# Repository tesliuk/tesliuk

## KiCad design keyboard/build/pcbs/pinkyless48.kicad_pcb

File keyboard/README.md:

# pinkyless48

A 48-key column-staggered split keyboard, designed around barely using your
pinkies. Kailh Choc v1 low-profile, hotswap, wired, RP2040 + QMK.

## The layout

24 keys per half:

```
 pinky  ring   mid   idx  inner
   O      O     O     O     O                  number row
   O      O     O     O     O                  top row
   O      O     O     O     O                  home row
   ·      O     O     O     O                  bottom row

                            O     O     O      thumb arc
                               O     O         thumb island
```

The thumb cluster starts where the finger matrix ends: the nearest thumb key
sits directly below the innermost finger column, and the cluster runs inboard
from there rather than being tucked back underneath the fingers.

The pinky drops only the **bottom row**, the position it reaches worst. It
keeps number, top and home. Because the number row therefore has all five
columns, it carries a full `1234567890` across the two halves and digits need
no layer. Z, Shift, Ctrl, Tab, Esc, Enter and Backspace — the rest of what a
pinky normally carries — moved to the thumbs and to home-row mods.

Five thumb keys per half, in two groups: a 3-key arc that follows the thumb's
natural sweep inboard and down, and a 2-key island tucked below it for the
keys you press less often. The furthest is 42 mm from the thumb home key,
inside the ~45 mm a relaxed thumb can sweep without the hand leaving position.

Column stagger is deliberately flat: inner, index and ring all sit level with
each other, middle is 4 mm further forward, and pinky drops **12 mm** back.
This is not the usual finger-length stagger — only the middle finger gets
extra reach.

The pinky drop is larger than it looks like it needs to be, on purpose. That
column carries three keys and skips the *bottom* row, so its block occupies
the upper three row positions. With a small stagger the column reads as
sitting higher than its neighbours even though every individual key is lower;
12 mm brings the whole block down to where a short finger actually rests.

One consequence worth knowing: the reversible Choc hotswap footprint carries
socket pads for *both* faces of the board and is ±9.58 mm wide, so two columns
at the *same* height short against each other at an 18 mm pitch. Index and
inner are level, so that single gap is opened to **19.8 mm**. Every other gap
stays at 18 mm, clearing on vertical offset alone.

Key pitch is **18.5 × 18 mm**, slightly looser than the 18 × 17 Choc standard.
Stock spacing leaves only 0.5 mm between MBK keycaps and 2.0 mm between switch
flanges, which works but is tight for getting a puller in and leaves nothing
for caps larger than MBK. This gives 1.0 mm between caps, 1.5 mm down rows and
3.0 mm between flanges, for ~2 mm of width and ~3 mm of height.

Board: **141 × 138 mm** per half. Case: **8.9 mm** tall before switches.
The width comes from the thumb cluster reaching ~37 mm inboard of the matrix.

The controller, TRRS jack and reset button live in the **notch** between the
finger matrix and the thumb cluster, not on a strip above the matrix. Because
the thumb cluster runs inboard and down, that area is dead space already
inside the bounding box, so the controller costs nothing in overall size —
putting it above the matrix instead added 30 mm of board height for a part
that is 33 × 18 mm. The USB port faces inboard, so the cable exits between
the halves.

The board silhouette is built from **three simple shapes**, not from one
rectangle per key: the finger matrix as a single rectangle, the thumb cluster
as a hull over its five keys, and the controller area as a rectangle. Unioning
24 key pads plus a rotated thumb cluster used to produce an outline of ~50
entities full of little scallops and fillets, which is miserable to build a
case against. The result now is **9 straight lines and 12 arcs**, for about
1 cm² more copper.

The union is then **morphologically closed** (grown 18 mm, shrunk 18 mm) before
filleting. That fills the concave pockets between the thumb cluster, the
controller area and the key pads — dead space whose sharp inside corners are
crack initiation points in both FR4 and the printed plate. It costs 1.3% more
board area and nothing in bounding box, and keeps the narrowest neck above 50 mm. Each half is closed separately —
closing them together would bridge the gap between the halves and fuse them. A plain convex hull would have swallowed the whole empty
region left of the thumb cluster and added ~40 cm² of pointless board.

## What is in here

```
src/config.yaml        the single source of truth - layout, nets, footprints
src/check_*.py         five verification passes, run by `make check`
src/find_mounts.py     searches the board for valid screw positions
case/gen_case.py       plate + tray STLs, generated from the same key positions
firmware/gen_qmk.py    generates keyboard.json from the same key positions
firmware/pinkyless48/  QMK keymap
build/                 generated outputs (committed - they are the deliverable)
docs/ORDERING.md       how to get it made with almost no soldering
docs/PIN_MAPPING.md    controller pins, matrix cells, debugging a bad matrix
```

Everything downstream — PCB, case, firmware — is derived from `src/config.yaml`.
Change a dimension there, run `make`, and the board, the STLs and the keymap
all follow. Nothing is hand-maintained in two places.

## Build it

```sh
make deps      # npm install + python deps
make           # build, check, case, firmware
```

`make check` runs five passes and fails loudly:

| Check | Catches |
|-------|---------|
| `layout` | **minimum** keycap and switch-flange gaps (not just overlap), for two cap sizes; thumb keys out of reach |
| `outline` | disconnected pieces; stray voids; missing screw holes; **thin necks and concave notches** |
| `matrix` | miswired switch/diode; **two keys sharing a matrix cell** |
| `fit` | components or screws hanging off the board edge |
| `shorts` | **pads on different nets overlapping**; copper clearance |

These are not decoration. Building this design they caught, among others: the
thumb cluster coming out as four disconnected board fragments; seven short
circuits where the controller and TRRS jack overlapped the number-row
switches; and the socket-pad short between the two level columns that forced
the 19.8 mm inner pitch. Every one would have produced a dead board at full
cost.

## Before you order boards

**The PCB is placed and netlisted but not routed.** Ergogen does not route
traces. Open the board in KiCad, route the matrix, pour ground, run DRC, and
plot gerbers. Full instructions in [docs/ORDERING.md](docs/ORDERING.md) —
please read it before spending money.

## Printing the case

Four STLs in `build/case/`: `plate_left`, `plate_right`, `tray_left`,
`tray_right`. All watertight, all flat-bottomed, no supports needed.

- **Plate** — 1.3 mm, prints on its back. Choc switches clip into the 13.8 mm
  cutouts. Print in PETG or ABS if you can; 1.3 mm of PLA is a little brittle
  around the cutouts.
- **Tray** — 0.2 mm layers, 3 perimeters, 20 % infill.

Stack, from the tray floor: 2 mm floor, 4 mm gap for the hotswap sockets,
1.6 mm PCB, 1.3 mm plate. Six M2 × 6 mm self-tapping screws go down through
the plate and PCB into the printed bosses.

The controller and TRRS jack sit *above* the plate, through the opening in the
notch beside the thumb cluster — the controller is socketed on headers, so it
stands proud. That is normal for a DIY split and keeps the USB port and jack
accessible without any wall cutouts.

## Adjusting it

The pinky rows, thumb positions and column stagger are all named values at the
top of `src/config.yaml`. Three things worth knowing before you edit:

- Ergogen's `stagger` is **cumulative**, not absolute. The config works around
  this by writing each column as `st_this - st_previous`, so you can edit the
  absolute numbers and the deltas take care of themselves.
- The thumb cluster is anchored to `matrix_inner_bottom` with t1 at an
  x-shift of exactly 0, so the nearest thumb key stays aligned with the last
  finger column and the cluster always begins where the matrix ends. Add or
  remove a finger column and the cluster follows. To slide the whole cluster,
  change that one x-shift rather than editing all five.
- After moving anything, run `make mounts` to re-derive screw positions and
  paste the result back into the `mounts` zone. Screw positions depend on the
  layout, and a screw that lands in a switch cutout leaves that switch with
  nothing to clip into.

Then `make check`. Do not order boards from a red tree.

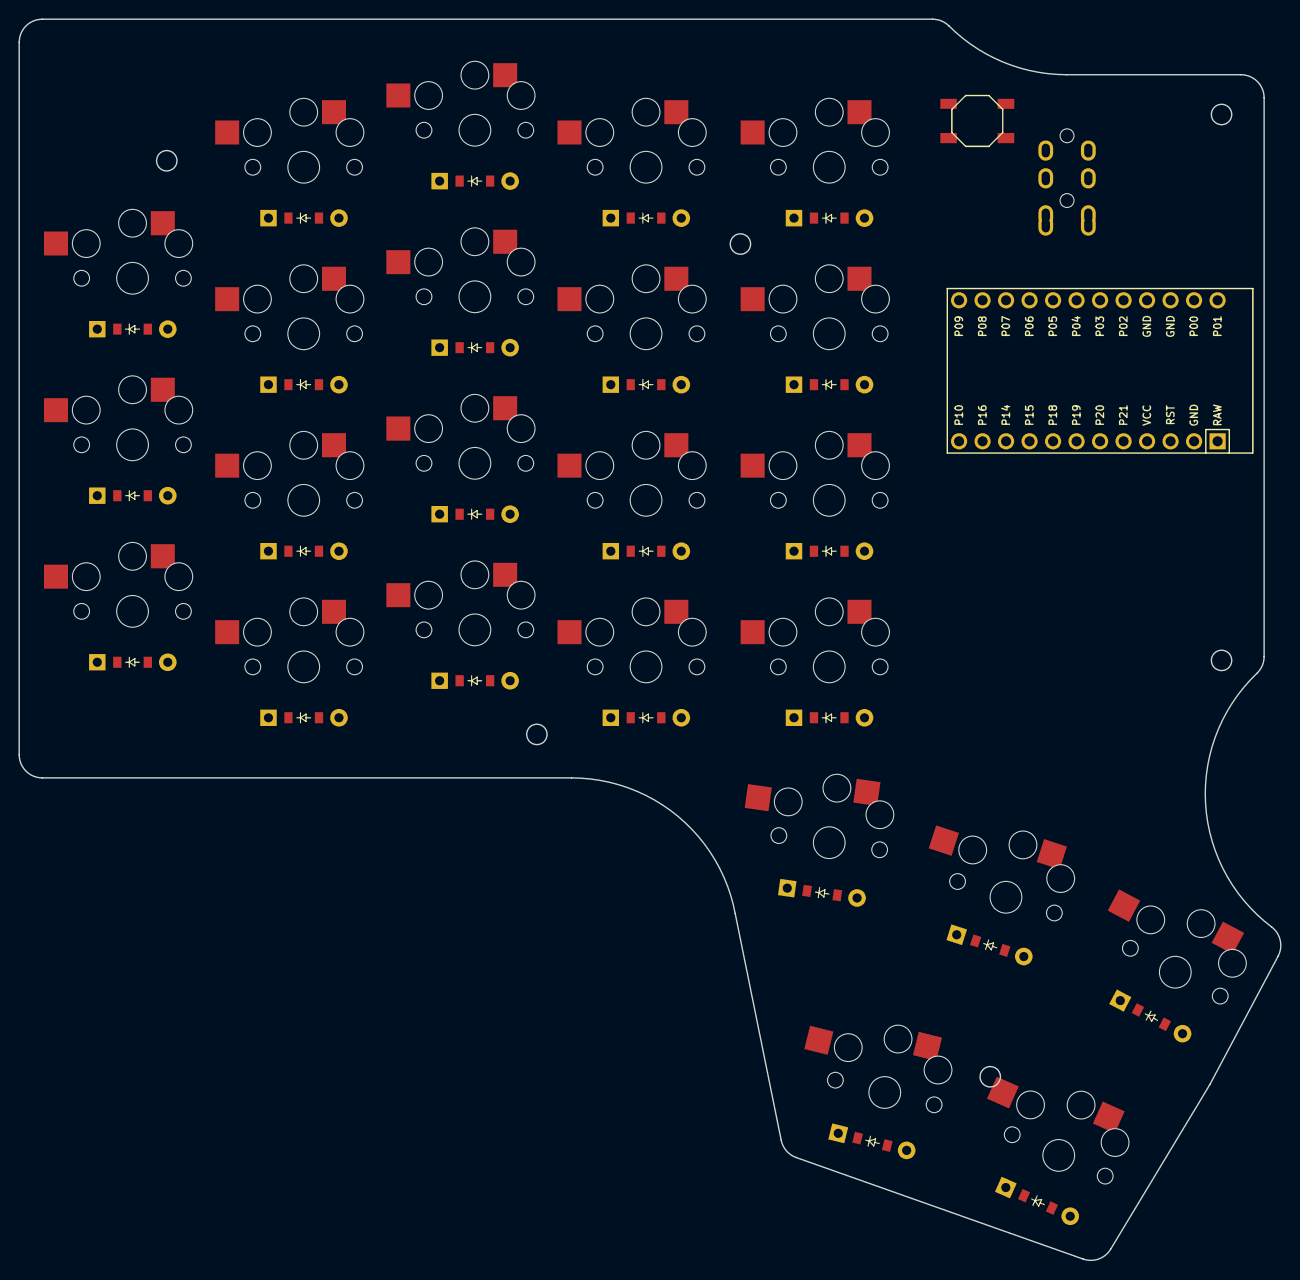
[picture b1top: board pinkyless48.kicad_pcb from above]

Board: 2 copper layers, 136.4 x 134.1 mm, 51 parts (0 on the bottom side), 38 nets, no tracks yet.

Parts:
B1: SW_TACT_ALPS_SKQGABE010
D1, D2, D3, D4, D5, D6, D7, D8, D9, D10, D11, D12, D13, D14, D15, D16, D17, D18, D19, D20, D21, D22, D23, D24: ComboDiode
MCU1: ProMicro
S1, S2, S3, S4, S5, S6, S7, S8, S9, S10, S11, S12, S13, S14, S15, S16, S17, S18, S19, S20, S21, S22, S23, S24: PG1350
TRRS1: TRRS-PJ-320A-dual

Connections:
C1: MCU1.22, S1.2, S2.2, S3.2, S20.2
C2: MCU1.23, S4.2, S5.2, S6.2, S7.2, S21.2
C3: MCU1.24, S8.2, S9.2, S10.2, S11.2, S22.2
C4: MCU1.8, S12.2, S13.2, S14.2, S15.2, S23.2
C5: MCU1.7, S16.2, S17.2, S18.2, S19.2, S24.2
DATA: MCU1.13, TRRS1.4
GND: B1.2, MCU1.2, MCU1.15, MCU1.16, TRRS1.1, TRRS1.2
R1: D4.1, D8.1, D12.1, D16.1, MCU1.17
R2: D1.1, D5.1, D9.1, D13.1, D17.1, MCU1.18
R3: D2.1, D6.1, D10.1, D14.1, D18.1, MCU1.19
R4: D3.1, D7.1, D11.1, D15.1, D19.1, MCU1.20
R5: D20.1, D21.1, D22.1, D23.1, D24.1, MCU1.21
RST: B1.1, MCU1.3
VCC: MCU1.1, MCU1.4, TRRS1.3
index_bottom: D12.2, S12.1
index_home: D13.2, S13.1
index_num: D15.2, S15.1
index_top: D14.2, S14.1
inner_bottom: D16.2, S16.1
inner_home: D17.2, S17.1
inner_num: D19.2, S19.1
inner_top: D18.2, S18.1
middle_bottom: D8.2, S8.1
middle_home: D9.2, S9.1
middle_num: D11.2, S11.1
middle_top: D10.2, S10.1
pinky_home: D1.2, S1.1
pinky_num: D3.2, S3.1
pinky_top: D2.2, S2.1
ring_bottom: D4.2, S4.1
ring_home: D5.2, S5.1
ring_num: D7.2, S7.1
ring_top: D6.2, S6.1
t1_thumb: D20.2, S20.1
t2_thumb: D21.2, S21.1
t3_thumb: D22.2, S22.1
t4_thumb: D23.2, S23.1
t5_thumb: D24.2, S24.1
